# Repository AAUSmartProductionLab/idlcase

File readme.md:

## Overview

This repository contains everything related to the Industrial data logger suitcase, including Raspberry Pi configuration in `ansible/`, firmware for actual devices (`espBME280/`, `espButton` ... ) and `dash/` which glues a lot of stuff together.

## Concept drawing

Data flows from sensors, though MQTT where `dash` listens for events which it then passes on to the GUI of the Raspberry Pi and stores it in the database.
 
Users access a Grafana frontend where they will be able to browse time series data directly from the database.
All the above software runs locally on the Raspberry Pi

## Connectivity
Raspberry Pi(s) continuously tries to join a VPN with our cloud server - the cloud server acts as a reverse proxy and passes HTTP requests for configured domains directly to the Raspberry Pis inside the VPN. Traffic not inside the VPN and also not directly connected to the Pi's wifi network will be rejected.

## Firmware over-the-air updates
The OTA scheme implemented tries to solve two scenarios
* A developer sits in platformio and wants to update all BME280 sensor devices
* A case is pulled out - some BME280 sensors are updated, some are not - those that are not should be able to update themselves without anyone touching the IDE

To solve these scenarios, the `dash/` projects host simple JSON files describing the latest version of a given firmware type - When a device cold boots, it will try to compare its release to the one fetched from `dash`.

When a developer wants to upload new firmware, `idlversion` and `idluploader` helps figuring out what version number to use next, when running "Upload" it will upload the firmware to the IDL case and publish a message on MQTT which devices listen to. Devices then to the regular OTA update just as if hey where cold booted.

## WifiManager
Our Library IDLNetworking makes use of [tzapu's wifimanager](https://github.com/tzapu/WiFiManager/tree/development). If the ESP device cannot connect to a known wifi it will start the wifimanager. The device will create a hotspot named "CONFIGURE ME - 12AB34" with the ending being the device ID. When connecting to this hotspot all traffic will be routed to a configuration portal that can be accecced with any browser. Connecting from an Android device this portal pops up by itself via a notification. Is that not the case the portal can be accessed on ip address `192.168.1.4`. 
From the portal it is possible to select any nearby access point and type in the password for it. As well as selecting access point it is also possible to set the MQTT server and port to publish on. Finally you can set the server where the ESP-device will check for firmware updates.
Writing `true` into the field named "use defaults below" will set MQTT and firmware server to the ip of gateway.
The protal is kept open for 5 minutes before the device tries to connect to known wifi again.  
Known bugs: wifimanager opens the configuration portal on every other reset. See issue [#1067](https://github.com/tzapu/WiFiManager/issues/1067) for updates. 

## BOM
Raspberry Pi
Raspberry Pi display
4G GSM dongle
esp32 devices and sensors

## MQTT namespaces and Datatypes
Two high-level namespaces exist at the moment, `idl` and `idlota`

### /idl/<deviceID>/<messageType>
Used for incoming events and metrics, `dash` assumes data is metric by default. `<deviceID>`, is used to tag the data and `<messageType` is dictating the format of the json payload. Two message-type formats exists, `events` and `measurements`. Common for both formats is the massages are in an array with an object for each measurement and event. Be aware that the formats does not mix. One array must contain only one format type chosen by the MQTT toppic

**Examples of Metric topics and their payloads:**
```
/idl/C4B3CC/measurements
[
    {       
        "table": "temperature",     // influxdb tabel
        "name": "sensor 1",         // influxdb tag
        "unit": "celcius",          // influxdb tag
        "value": 23.34,             // influxdb value
        "tags":{                    // optional extra tags
            "placement" : "kitchen"
        }
    },
]
```
**Event message**
```
/idl/1C8781/events
[
    {       
        "table": "events",                      // influxdb tabel
        "msg": "someone pushed the red button", // human readable 
        "payload": "{blob}",                    // whatever one sees fit
        "tags": {                               // optional extra tags
            "color":"red",
            "priority": "1",
        }
    },
]
```
**Multiple measurements**
```
/idl/1C8781/measurements
[
    {       
        "table": "temperature",
        "name": "BME280",
        "unit": "celsius",
        "value": 20.5,
    },
    {       
        "table": "microphone",
        "name": "left channel",
        "unit": "dBm",
        "value": 42.47,
        "tags": { 
            "band":"100hz",
        }
    },
    {       
        "table": "microphone",
        "name": "left channel",
        "unit": "dBm",
        "value": 51.25,
        "tags": { 
            "band":"200hz",
        }
    },
    {       
        "table": "microphone",
        "name": "right channel",
        "unit": "dBm",
        "value": 42.87,
        "tags": { 
            "band":"100hz",
        }
    },
    {       
        "table": "microphone",
        "name": "right channel",
        "unit": "dBm",
        "value": 50.15,
        "tags": { 
            "band":"200hz",
        }
    },
]
```

### /idlota topics
These topics are used to announce firmware updates to running devices. There is no payload and publishes to this topic makes sure interested devices check the OTA service for updates.

## Legal
Copyright 2020 Aalborg University
MIT License

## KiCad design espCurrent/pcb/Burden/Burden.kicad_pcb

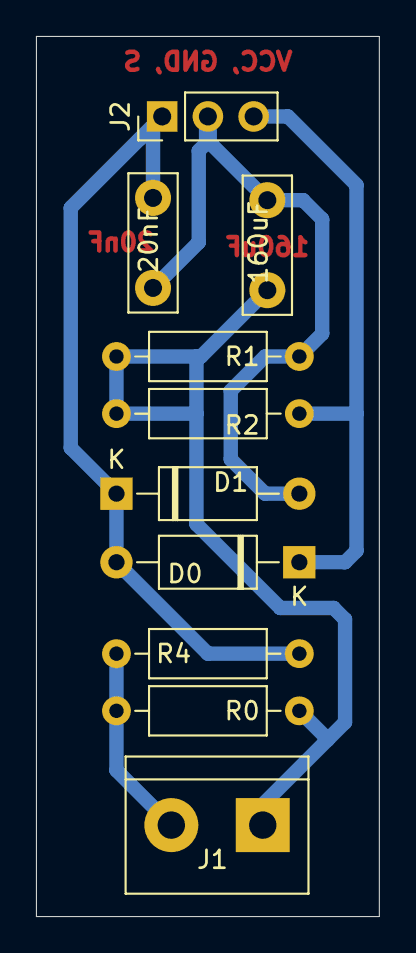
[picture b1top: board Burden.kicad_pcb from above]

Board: 2 copper layers, 19.0 x 48.9 mm, 10 parts (0 on the bottom side), 5 nets.

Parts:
20nF, 160uF: C; C_Disc_D7.5mm_W2.5mm_P5.00mm
D0, D1: D; D_A-405_P10.16mm_Horizontal
J1: Screw_Terminal_01x02; TerminalBlock_bornier-2_P5.08mm
J2: Conn_01x03; PinHeader_1x03_P2.54mm_Vertical
R0: R330; R_Axial_DIN0207_L6.3mm_D2.5mm_P10.16mm_Horizontal
R1, R2: R100k; R_Axial_DIN0207_L6.3mm_D2.5mm_P10.16mm_Horizontal
R4: R10K; R_Axial_DIN0207_L6.3mm_D2.5mm_P10.16mm_Horizontal

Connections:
/V_sense: 20nF.2, D0.2, D1.1, J2.1, R4.2
GND: 20nF.1, 160uF.2, D1.2, J2.2, R1.2
unnamed: 160uF.1, J1.1, R0.2, R1.1, R2.2
unnamed: J1.2, R0.1, R4.1
VCC: D0.1, J2.3, R2.1

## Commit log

2020-01-14 Added dash and Makefile
2020-01-14 Dont show addresses we dont care about
2020-01-14 Makefile: build dashboard
2020-01-14 Ansible: ignore dash-build
2020-01-14 Rename dash binary
2020-01-14 ansible_become is boolean ... oops
2020-01-14 Ansible: dash role
2020-01-14 Add dash role to case
2020-01-14 Changed some UI texts
2020-01-14 Ansible: Takeover tty1 and reload dash if changes are made to tty1
2020-01-14 Ansible: Moved stuff around
2020-01-14 Changed inventory with new raspberry ip address
2020-01-14 Add fingerprint to knownhosts
2020-01-14 Ansible: install and configure hostapd
2020-01-14 ansible: configure ip address for wlan0
2020-01-14 We are handing out ip adresses, hopefully only on wlan0
2020-01-15 Manage eth0 with networkd - remove ifupdown and disable dhcpcd
2020-01-15 Add hardcoded dns servers
2020-01-15 Ansible: Install influxdb
2020-01-15 Ansible: install grafana
2020-01-15 Ansible: ability to skip roles when developing
2020-01-16 Dash: Moved status logic out of main.go
2020-01-16 Dash: Changed some strings
2020-01-16 Ansible: renamed task names to follow other task's naming scheme
2020-01-16 Ansible: install mosquitto
2020-01-20 Dummy IoT Device
2020-01-21 Moved gui out of the way
2020-01-21 Changed json payload to be actural json :)
2020-01-21 Dash: Its now able to show some sensor data
2020-01-22 Moved stuff around
2020-01-22 Sensor: somewhat working espBME280 sensor
2020-01-22 Changed the deviceID, changed "bs" unit
2020-01-22 dash: Sensor view is now more readable
2020-01-22 dash: We are now storing data in influxdb
2020-01-23 ansible: as aau's network is broken - specify list of NTP servers
2020-01-24 dash: Made the Sensor view more human readable
2020-01-24 ansible: ensure wvdial is installed to dial the modem
2020-01-27 ansible: Added wvdial configurtation for telenor
2020-01-27 esp: code for handling buttons and sending events
2020-01-31 espButton: Changed name of event
2020-01-31 dash: Work regarding support for different message types
2020-02-03 In the case of no wifi connection, try to reconnect to wifi before trying to reconnect to MQTT
2020-02-03 esp: fixed reconnect bug
2020-02-03 dash: Handle influxdb errors without panicing
2020-02-03 ansible: send logging from dash into journal
2020-02-05 Repository change
2020-02-05 dash: we are able to serve firmware for devices
2020-02-05 ansible: Ignore hidden ansible directory
2020-02-05 dash/fota: ability to accept http posted files locally
2020-02-06 Save point
2020-02-06 docs: Started on readme and added drawing
2020-02-07 fota: ability to accept and announce new firmwares
2020-02-10 fota: ability to push updates
2020-02-11 idlota: various scripts for uploading firmware
2020-02-11 espButton: enable ota updates
2020-02-11 espBME280: enable ota updates
2020-02-12 Makefile: add in the users ssh keyagent
2020-02-12 ansible: setup cloud vpn device and network
2020-02-13 ansible: remove access keys from repo and use personalized ssh keys
2020-02-13 ansible: install wireguard to raspberry pi
2020-02-13 ansible: connect to our aau vm
2020-02-13 ansible: wireguard communication is operational
2020-02-13 ansible: vpnclients only accepts traffic from wlan or vpn tunnel
2020-02-13 ansible: connect to raspberry pies though metric-log01
2020-02-13 ansible: Trust metric-log01's fingerprint
2020-02-17 ansible: added webgateway serving grafana directly from raspberry
2020-02-17 Updated documentation
2020-02-18 added rfidReader to the repo
2020-02-18 idlota: access the version database though ssh and share known_hosts with ansible
2020-02-18 fix: added version.h to gitignore
2020-02-18 update to exclude macos DS_Store file
2020-02-19 initial commit for library
2020-02-19 ansible: authorize keys from listed urls
2020-02-19 implementing OTA and bugfixes
2020-02-19 ansible: added warning about the authorized_keys
2020-02-19 implemented loop function
2020-02-19 reset function + bugfix
2020-02-19 implementing library. NOT WORKING
2020-02-19 added espLib path
2020-02-19 preliminary deletion of unnessesary code
2020-02-20 ansible: make sure an idl database exists
2020-02-20 Library working and example integrated on rfid
2020-02-20 Makefile: Build dash in docker
2020-02-24 ansible: dont use wvdial and instead relay on simple systemd services
2020-02-25 impl. of library done. could still need some love
2020-02-25 capital letter in measurement json changed consistensy
2020-02-27 ansible: webgateway: changed to aau.dk domain
2020-03-03 api: Added simple mqtt forwarder api
2020-03-03 ansible: build, upload and ensure api is running
2020-03-03 ansible: enable new api service to outside domain
2020-03-04 ansible: work in progress
2020-03-04 ansible: vpnserver configuration is now generated dynamicly
2020-03-04 ansible: create wireguard configuration for clients dynamically
2020-03-05 Added license
2020-03-05 ansible: store wifi credentials in inventory to allow customization
2020-03-23 working
2020-03-23 bugfixes and dithering implementation
2020-03-23 cleanup and better dithering algorithm
2020-03-24 add library.json and dummy main so lib can complie
2020-03-24 just formatting
2020-03-25 work in progress
2020-03-27 added idl networking
2020-03-27 bugfixes
2020-03-27 added get device id function
2020-03-27 added dislpay and fixed a buch of comments.
2020-03-27 formatting
2020-03-30 Simple way of connecting, from outside the aau network
2020-03-30 Added another raspberry pi to ansible
2020-03-30 IDLNetworking implemented + new json format
2020-04-02 Make fota tools use a persistent ssh connection
2020-04-02 working fota
2020-04-02 ota on start
2020-04-06 adding luminosity sensor esp module
2020-04-06 impl: idlNetworking and new mqtt message format
2020-04-07 Restored from espFFT2 branch
2020-05-06 Include all hosts on 10.14.47.0/24 in ssh_config
2020-06-24 Changed mqtt topic, added some code to convert measurements into influxdb rows
2020-06-26 initial commit. working first version
2020-06-26 fixed timing issue so it now publises more presice
2020-06-29 bugfixes and minor changes.
2020-07-06 Updated for new library changes
2020-07-06 Serious updates + cleanup of library. many changes
2020-07-07 change controlPersist to 1 minute instead of 1hour
2020-07-07 adde tags to messages + minor tweaks.
2020-07-07 fixes for newest version of espLib
2020-07-08 update devices for new library + bugfixes
2020-07-08 New model
2020-07-08 implement new lib. + alternative onewire lib.
2020-07-10 renamed and fixed espRFID firmware
2020-07-10 hotfix for events. change "message" to "msg"
2020-07-10 update namespaces and datatypes.
2020-07-10 better examples
2020-08-10 changed to dynamicJsonDocument + timeing fix
2020-08-10 disable warning message if interval = 0
2020-08-10 fix my fix
2020-10-14 New case: added grundfos idl case
2020-10-29 api: current values work in progress
2020-10-29 api: last values endpoints finished
2020-11-02 api: removed unused dependencies
2020-11-10 major espRFID overhaul
2020-11-10 initialize deviceid and version in constructor
2020-11-10 small changes. added autoconnect bool
2020-11-10 major overhaul. lots of new features.
2020-11-10 cleanup lib_deps. new fota version
2020-11-10 documentation
2020-11-10 added ir_analog_distance. code derived from rfid
2020-11-10 ascii art headder
2020-11-10 cleanup and commets
2020-11-10 minor cleanup and commet
2020-11-10 cleanup and comments
2020-11-17 wifimanager initial descirption
2020-11-17 bug note about wifimanager added
2020-11-19 Readme wifi manager (#1)
    * wifimanager initial descirption
    * bug note about wifimanager added
2020-11-19 fix:spelling mistake
2020-11-19 add: readme for devices
2020-11-19 minor changes
2020-11-19 energy: users, ntp config and hostapd in master and client mode
2020-11-20 energy: renamed hostapd role to networking
2020-11-20 networking: use hardcoded pool of NTP servers
2020-11-20 networking: ask for ssid and passphrase, docs about maintenance
2020-11-23 energy: install mbmd
2020-11-26 energy: various fixes to make it all fit together
2020-12-03 bugfixes for setting defaults
2020-12-11 Energy sensor (#3)
    * energy: users, ntp config and hostapd in master and client mode
    * energy: renamed hostapd role to networking
    * networking: use hardcoded pool of NTP servers
    * networking: ask for ssid and passphrase, docs about maintenance
    * energy: install mbmd
    * energy: various fixes to make it all fit together
2020-12-11 More readme (#2)
    * fix:spelling mistake
    * add: readme for devices
    * minor changes
2021-01-07 analog sensor pins first commit
2021-01-07 analog pins done and added
2021-01-07 bugfix
2021-01-07 fix: commented out upload scirpts
2021-01-08 Bugfixes and more (#4)
    * fix:spelling mistake
    * add: readme for devices
    * minor changes
    * bugfixes for setting defaults
    * bugfix
2021-01-08 Analog sense pins (#5)
    * fix:spelling mistake
    * add: readme for devices
    * minor changes
    * bugfixes for setting defaults
    * analog sensor pins first commit
    * analog pins done and added
2021-01-14 first prototype. has corrupt data
2021-01-18 3d printed house v1
2021-01-18 cleanup and working integration
2021-01-18 analog activation pin change, spelling and fixes.
2021-01-18 HOTFIX: wifi recconect portal timout set to 1 sec.
2021-01-19 redesign: reinforcement and size increase
2021-01-26 new flow calculations
2021-01-26 pin change and libs
2021-02-25 ip update. add keys. minor fixes
2021-02-25 pcb for burden resistor and over voltageprotection
2021-02-25 esp current src first commit
2021-02-25 change wifiportal timeout
2021-02-25 Esp custom fixes (#10)
    * analog activation pin change, spelling and fixes.
    * new flow calculations
    * change wifiportal timeout
2021-03-05 Esp current (#8)
    * pcb for burden resistor and over voltageprotection
    * esp current src
2021-03-05 ip update. add keys. minor fixes (#7)
2021-03-05 pin change and libs (#9)
2021-03-08 wg keys stored in files
2021-03-08 using slurp to read files
2021-03-09 linebreak removed
2021-03-11 lib update
2021-03-11 test
2021-03-11 Development (#12)
    * lib update
2021-03-11 removed development tag on wifimanager lib.
2021-03-12 get started added
2021-03-17 Fully automating the installation of wireguard
2021-03-18 remove notes
2021-03-18 finaliseing guide
2021-03-18 whitespace remove
2021-03-18 adding new devices to inventory
2021-03-18 whitespace
2021-03-22 change to arduino version of mpu lib
2021-04-28 Create .gitattributes
    this excludes g-code files for the github language statistics.
